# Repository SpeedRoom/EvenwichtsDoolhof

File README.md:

# EvenwichtsDoolhof
Meer info over het project is te vinden op [https://speedroom.github.io/](https://speedroom.github.io/Evenwichts_Doolhof.html)

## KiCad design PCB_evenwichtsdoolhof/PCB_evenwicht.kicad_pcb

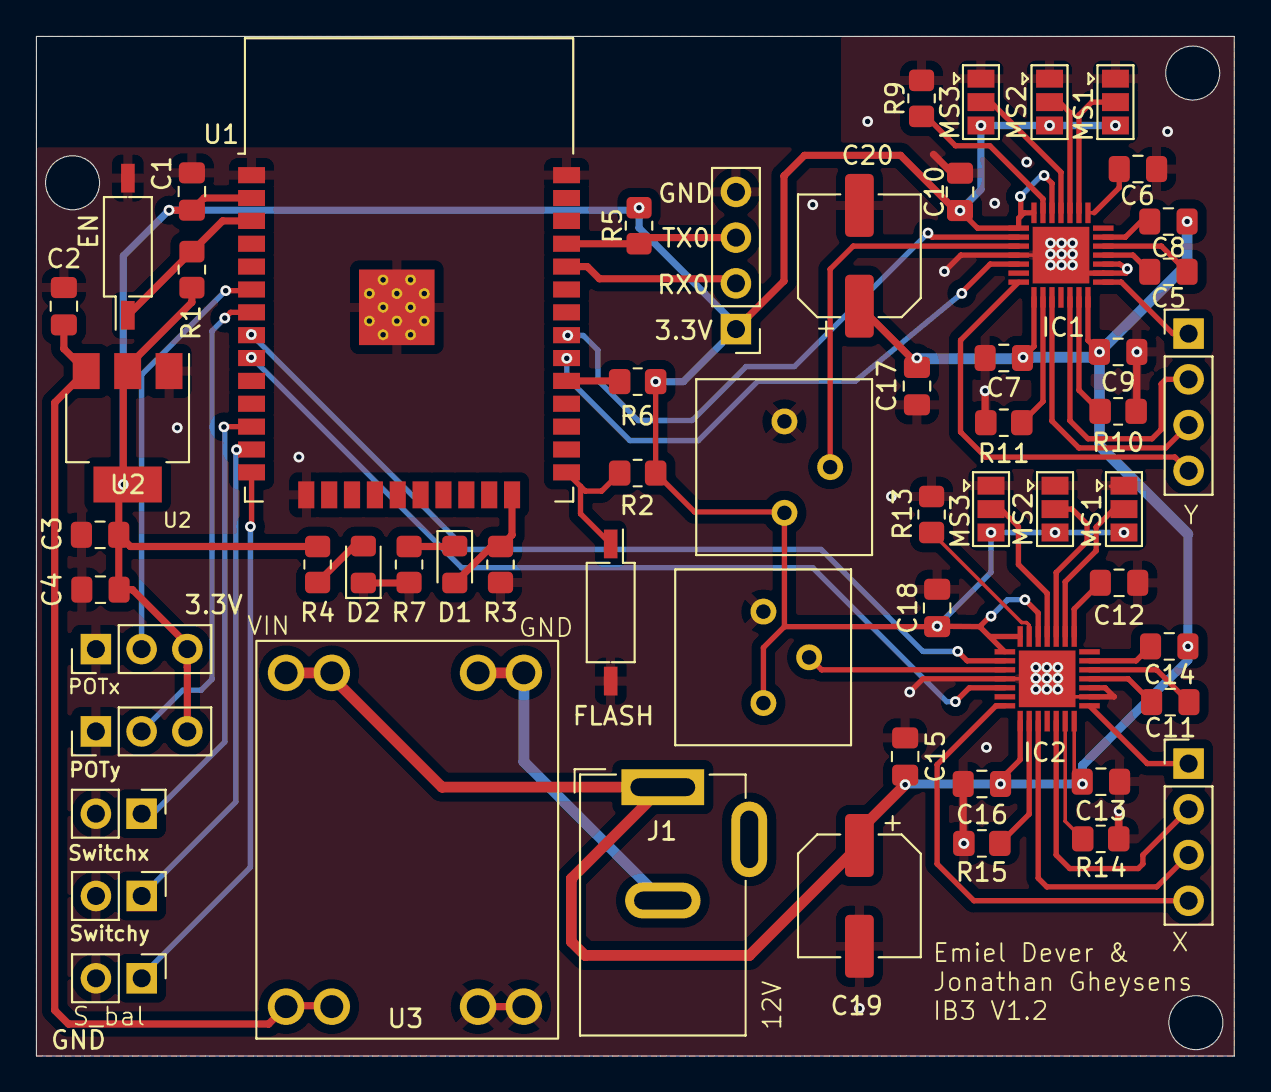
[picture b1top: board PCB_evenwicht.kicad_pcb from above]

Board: 2 copper layers, 66.5 x 56.6 mm, 59 parts (0 on the bottom side), 52 nets.

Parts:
C1: 100uF/6.3V; C_0805_2012Metric_Pad1.18x1.45mm_HandSolder
C2, C4: 10uF; C_0805_2012Metric_Pad1.18x1.45mm_HandSolder
C3, C7, C9, C13, C16: 100nF; C_0805_2012Metric_Pad1.18x1.45mm_HandSolder
C5, C11: 0.1u; C_0805_2012Metric_Pad1.18x1.45mm_HandSolder
C6, C10, C12, C18: 0.22uF; C_0805_2012Metric_Pad1.18x1.45mm_HandSolder
C8, C14: 0.1 uF; C_0805_2012Metric_Pad1.18x1.45mm_HandSolder
C15, C17: 4.7uF; C_0805_2012Metric_Pad1.18x1.45mm_HandSolder
C19, C20: 47uF; CP_Elec_6.3x5.9
D1: BLUE; LED_0805_2012Metric_Pad1.15x1.40mm_HandSolder
D2: PWR; LED_0805_2012Metric_Pad1.15x1.40mm_HandSolder
IC1, IC2: A4988SETTR-T; QFN50P500X500X100-29N
J1: Barrel_Jack; BarrelJack_GCT_DCJ200-10-A_Horizontal
J2, J4, J6: Conn_01x04_Pin; PinHeader_1x04_P2.54mm_Vertical
J3: Switchy; PinHeader_1x02_P2.54mm_Vertical
J5: POTy; PinHeader_1x03_P2.54mm_Vertical
J7: Switchx; PinHeader_1x02_P2.54mm_Vertical
J8: POTx; PinHeader_1x03_P2.54mm_Vertical
J9: Switch_einde; PinHeader_1x02_P2.54mm_Vertical
JP1, JP4: MS3; SolderJumper-3_P1.3mm_Open_Pad1.0x1.5mm
JP2, JP5: MS2; SolderJumper-3_P1.3mm_Open_Pad1.0x1.5mm
JP3, JP6: MS1; SolderJumper-3_P1.3mm_Open_Pad1.0x1.5mm
R1, R2, R3, R5, R6: 10K; R_0805_2012Metric_Pad1.20x1.40mm_HandSolder
R4, R7: 1K; R_0805_2012Metric_Pad1.20x1.40mm_HandSolder
R9, R13: 25K; R_0805_2012Metric_Pad1.20x1.40mm_HandSolder
R10, R11, R14, R15: 50m; R_0805_2012Metric_Pad1.20x1.40mm_HandSolder
RV1, RV2: R_Potentiometer; Potentiometer_Bourns_3386P_Vertical
SW1: EN; SW_DIP_SPSTx01_Slide_Copal_CHS-01B_W7.62mm_P1.27mm
SW2: FLASH; SW_DIP_SPSTx01_Slide_Copal_CHS-01B_W7.62mm_P1.27mm
U1: ESP32-WROOM-32
U2: AMS1117-3.3; SOT-223-3_TabPin2
U3: MP1584; U1584

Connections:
+3.3V: C1.1, C3.2, C4.1, C10.1, C18.1, IC1.12 (~RESET), IC1.14 (~SLEEP), IC1.15 (VDD), IC2.12 (~RESET), IC2.14 (~SLEEP), IC2.15 (VDD), J2.1, J5.3, J8.3, JP1.3 (B), JP2.3 (B), JP3.3 (B), JP4.3 (B), JP5.3 (B), JP6.3 (B), R1.1, R2.1, R4.1, R5.1, R6.1, RV1.1, RV2.1, U1.2 (VDD), U2.2 (VO)
/ESP32/EN: R1.2, SW1.1, U1.3 (EN)
A4: IC2.16 (STEP), U1.8 (IO32)
A5: IC2.19 (DIR), U1.9 (IO33)
GND: C1.2, C2.2, C3.1, C4.2, C6.2, C7.1, C9.2, C10.2, C12.2, C13.1, C15.1, C16.2, C17.1, C18.2, C19.2, C20.2, D2.1 (K), IC1.2 (~ENABLE), IC1.3 (GND_1), IC1.18 (GND_2), IC1.29 (EP), IC2.2 (~ENABLE), IC2.3 (GND_1), IC2.18 (GND_2), IC2.29 (EP), J2.4, J3.2, J5.1, J7.2, J8.1, J9.2, JP1.1 (A), JP2.1 (A), JP3.1 (A), JP4.1 (A), JP5.1 (A), JP6.1 (A), R3.1, R7.2, R9.1, R10.2, R11.2, R13.1, R14.2, R15.2, RV1.3, RV2.3, SW1.2, SW2.2, U1.1 (GND), U1.15 (GND), U1.38 (GND), U1.39 (GND), U2.1 (GND), U3.7 (OUT-), U3.8 (OUT-)
GPIO0: R2.2, SW2.1, U1.25 (IO0)
GPIO2: D1.2 (A), R3.2, U1.24 (IO2)
GPIO5: R6.2, U1.29 (IO5)
GPIO12: J9.1, U1.14 (IO12)
GPIO14: J3.1, U1.13 (IO14)
GPIO18: IC1.19 (DIR), U1.30 (IO18)
GPIO19: IC1.16 (STEP), U1.31 (IO19)
GPIO27: J7.1, U1.12 (IO27)
GPIO34: J8.2, U1.6 (IO34)
GPIO35: J5.2, U1.7 (IO35)
MS1_1: IC1.9 (MS1), JP3.2 (C)
MS1_2: IC2.9 (MS1), JP6.2 (C)
MS2_1: IC1.10 (MS2), JP2.2 (C)
MS2_2: IC2.10 (MS2), JP5.2 (C)
MS3_1: IC1.11 (MS3), JP1.2 (C)
MS3_2: IC2.11 (MS3), JP4.2 (C)
unnamed: D1.1 (K), R7.1
unnamed: D2.2 (A), R4.2
unnamed: C5.2, IC1.4 (CP1)
unnamed: C5.1, IC1.5 (CP2)
unnamed: IC1.24 (OUT1A), J4.3
unnamed: IC1.21 (OUT1B), J4.4
unnamed: IC1.26 (OUT2A), J4.2
unnamed: IC1.1 (OUT2B), J4.1
unnamed: IC1.17 (REF), RV1.2
unnamed: IC1.13 (ROSC), R9.2
unnamed: IC1.23 (SENSE1), R11.1
unnamed: IC1.27 (SENSE2), R10.1
unnamed: C8.2, IC1.6 (VCP)
unnamed: C6.1, IC1.8 (VREG)
unnamed: C11.2, IC2.4 (CP1)
unnamed: C11.1, IC2.5 (CP2)
unnamed: IC2.24 (OUT1A), J6.3
unnamed: IC2.21 (OUT1B), J6.4
unnamed: IC2.26 (OUT2A), J6.2
unnamed: IC2.1 (OUT2B), J6.1
unnamed: IC2.17 (REF), RV2.2
unnamed: IC2.13 (ROSC), R13.2
unnamed: IC2.23 (SENSE1), R15.1
unnamed: IC2.27 (SENSE2), R14.1
unnamed: C14.2, IC2.6 (VCP)
unnamed: C12.1, IC2.8 (VREG)
unnamed: J1.2, U3.1 (IN-), U3.2 (IN-)
RX0: J2.2, U1.34 (RXD0/IO3)
TX0: J2.3, R5.2, U1.35 (TXD0/IO1)
VDD: C2.1, U2.3 (VI), U3.5 (OUT+), U3.6 (OUT+)
Vmot: C7.2, C8.1, C9.1, C13.2, C14.1, C15.2, C16.1, C17.2, C19.1, C20.1, IC1.22 (VBB1), IC1.28 (VBB2), IC2.22 (VBB1), IC2.28 (VBB2), J1.1, U3.3 (IN+), U3.4 (IN+)

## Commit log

2023-02-21 lknj
2023-02-23 Goed?
2023-02-23 Finish
2023-02-23 Eindeloop werkend
2023-02-28 2 motoren
    werkende met 2 motoren en het begin van de detectie van het balletje geimplementeerd
2023-03-14 PCB_Design
    bcp design schematic voornameljik gedaan deel 1
2023-03-14 PCB_Update
    Nog enkel de footprints van de controller aanduiden en controleren van de waarden
2023-03-15 update pcb-design
2023-03-15 update pcb
2023-03-16 Update_Update
    PCB eens snel geroute
2023-03-21 fdqjmlk
2023-03-28 OTA added
2023-03-28 dqfsjmkmlqfd
2023-03-28 OTA updated
2023-04-20 goed
2023-04-26 Renaming files
2023-04-29 MQTT toegevoegd
2023-05-02 OTA gefixt
2023-05-02 stuklijst
2023-05-02 update 3
2023-05-02 3d print en laser cut
2023-05-02 update v4
2023-05-07 restructured
2023-05-08 MQTT fixed
2023-05-08 File Restructuring
    Restructuring and removing old files
    + cleaning up code
2023-05-09 box pcb
2023-05-09 qfdjmlk
2023-05-10 Files deleting
2023-05-10 Files deleting
    Deleting again
2023-05-14 box pcb + fill holes
2023-05-14 clean up 3d + lasercut
2023-05-14 clean up pcb
2023-05-14 csv file
2023-05-15 clean up
